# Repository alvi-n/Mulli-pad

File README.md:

# Mullipad
> By Alvin Nguyen

## 5-Key Macropad featuring: 
- Rotary Encoder (Knob)
- Full RGB backlighting using Neopixels 
- Small OLED screen 
- Recessed Base to give a _"floating"_ effect 
  
| "Woah this looks pretty cool" | "Same with this inside" |
| ----- | ---- |
|  |  |

## Details
This was a fun 3-week project to learn about PCB making, and it was fun modeling the case. It took a lot of questions on Slack and tutorials, but here it is. 

| Schematic | PCB |
| ----- | ---- |
|  |  |

### Future Plans
- I'm planning on using transparent 3d filament for the base so the light can glow on the bottom. This will also be used for my Hack Club at my school as an example project.
- The plate will be glued on...
- **The OLED screen will be connected to the pcb by wires which will be soldered on**

# BOM

| item | quantity |
| --- | --- |
| MX-Style switches | 5 |
| Blank DSA keycaps (White) | 5 |
| 0.91 inch OLED display | 1 |
| EC11 rotary encoder | 1 |
| Seeed xiao rp2040 | 1 |
| SK6812 mini-e led | 5 |
| 1x4 pin header | 1 |
| short f/f 1x4 pin header connector | 1 |
| M3x16mm screws | 4 |
| Case (Top, Plate, Bottom) | All 3D printed myself |

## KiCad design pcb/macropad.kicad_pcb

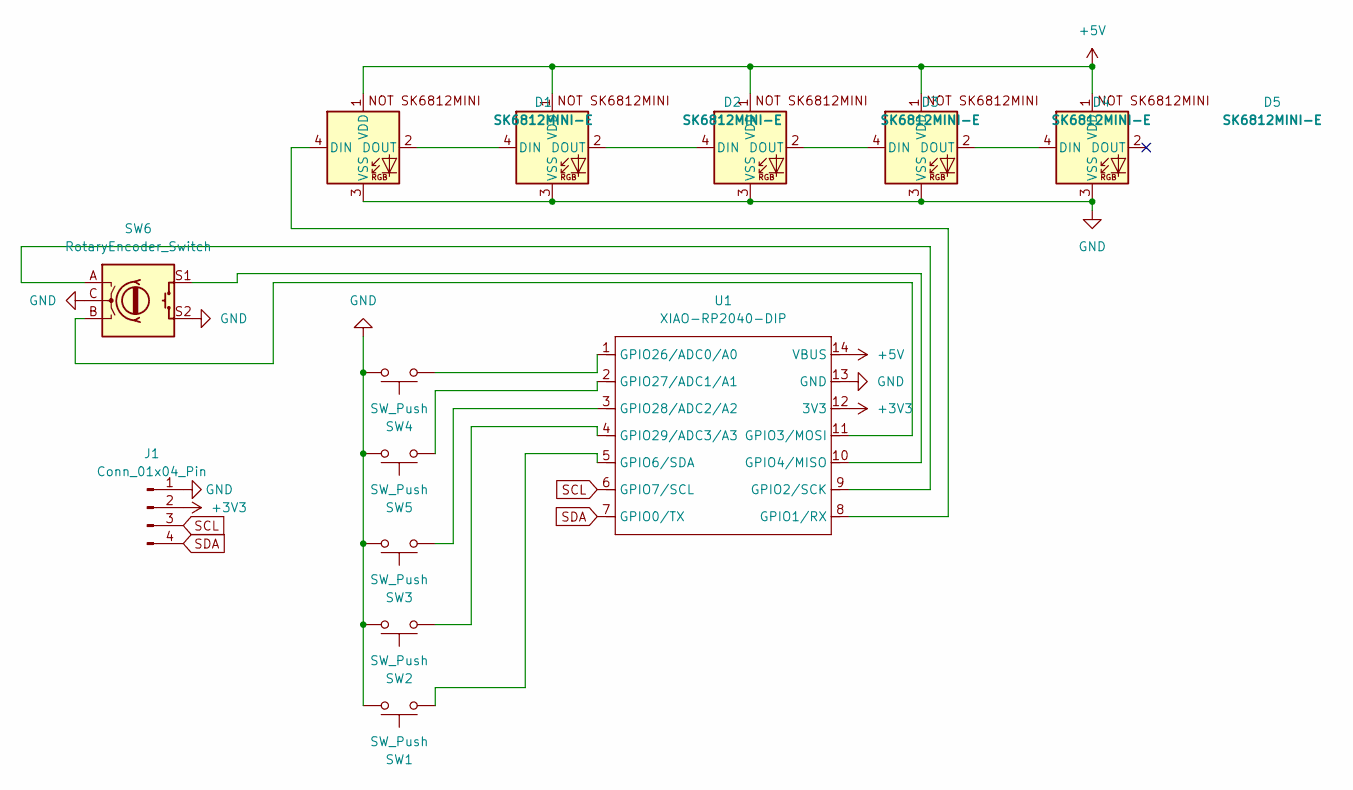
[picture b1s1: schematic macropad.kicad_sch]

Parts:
D1, D2, D3, D4, D5: SK6812MINI-E; SK6812MINI-E_fixed
J1: Conn_01x04_Pin; PinHeader_1x04_P2.54mm_Vertical
SW1, SW2, SW3, SW4, SW5: SW_Push; SW_Cherry_MX_1.00u_PCB
SW6: RotaryEncoder_Switch; RotaryEncoder_Alps_EC11E-Switch_Vertical_H20mm
U1: XIAO-RP2040-DIP

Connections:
+3V3: J1.2, U1.12 (3V3)
+5V: D1.1 (VDD), D2.1 (VDD), D3.1 (VDD), D4.1 (VDD), D5.1 (VDD), U1.14 (VBUS)
GND: D1.3 (VSS), D2.3 (VSS), D3.3 (VSS), D4.3 (VSS), D5.3 (VSS), J1.1, SW1.1, SW2.1, SW3.1, SW4.1, SW5.1, SW6.C, SW6.S2, U1.13 (GND)
unnamed: D1.4 (DIN), U1.8 (GPIO1/RX)
unnamed: D1.2 (DOUT), D2.4 (DIN)
unnamed: D2.2 (DOUT), D3.4 (DIN)
unnamed: D3.2 (DOUT), D4.4 (DIN)
unnamed: D4.2 (DOUT), D5.4 (DIN)
unnamed: SW6.A, U1.9 (GPIO2/SCK)
unnamed: SW6.B, U1.11 (GPIO3/MOSI)
unnamed: SW6.S1, U1.10 (GPIO4/MISO)
unnamed: SW1.2, U1.5 (GPIO6/SDA)
unnamed: SW4.2, U1.1 (GPIO26/ADC0/A0)
unnamed: SW5.2, U1.2 (GPIO27/ADC1/A1)
unnamed: SW3.2, U1.3 (GPIO28/ADC2/A2)
unnamed: SW2.2, U1.4 (GPIO29/ADC3/A3)
SCL: J1.3, U1.6 (GPIO7/SCL)
SDA: J1.4, U1.7 (GPIO0/TX)

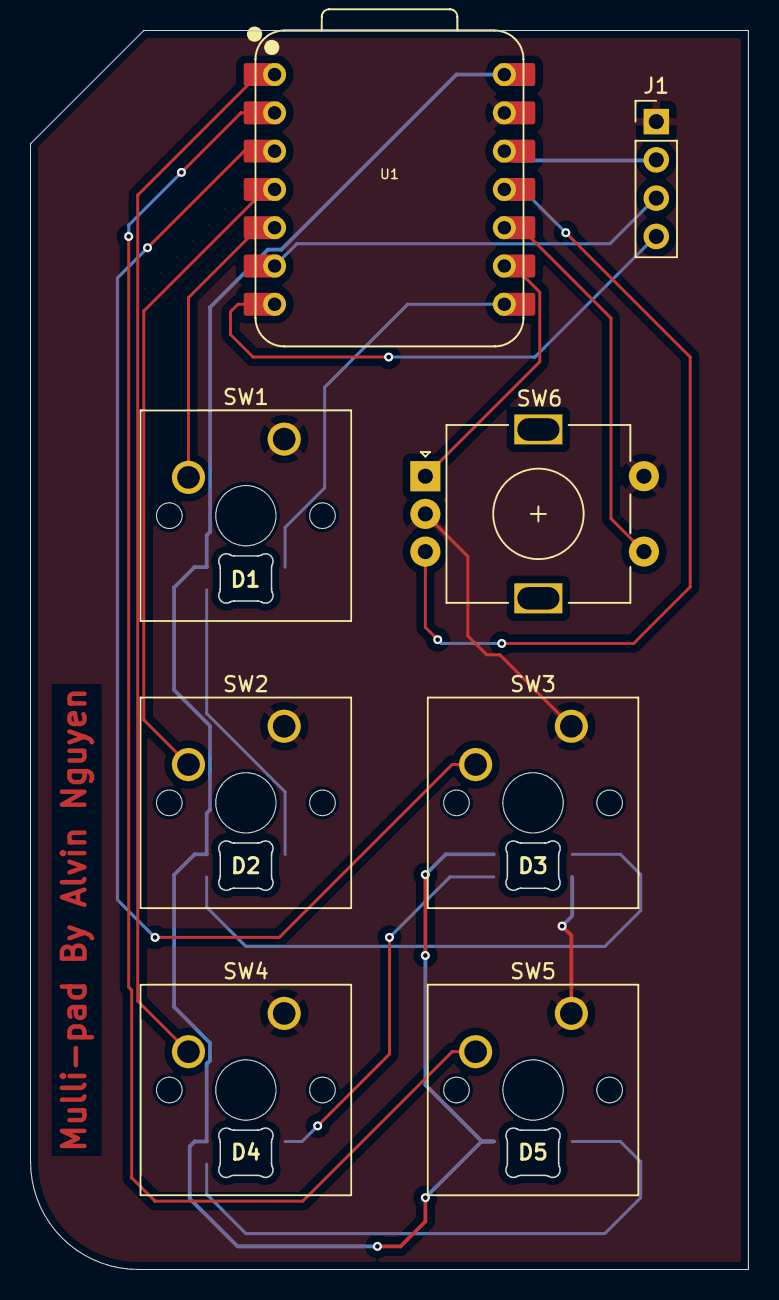
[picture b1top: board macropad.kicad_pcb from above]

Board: 2 copper layers, 47.6 x 82.1 mm, 13 parts (0 on the bottom side), 18 nets.

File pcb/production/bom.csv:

Designator,Footprint,Quantity,Value,LCSC Part #
"D1, D2, D3, D4, D5",SK6812MINI-E_fixed,5,SK6812MINI-E,
J1,PinHeader_1x04_P2.54mm_Vertical,1,Conn_01x04_Pin,
"SW1, SW2, SW3, SW4, SW5",SW_Cherry_MX_1.00u_PCB,5,SW_Push,
SW6,RotaryEncoder_Alps_EC11E-Switch_Vertical_H20mm,1,RotaryEncoder_Switch,
U1,XIAO-RP2040-DIP,1,XIAO-RP2040-DIP,

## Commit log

2026-01-30 Upload all project folders
2026-02-02 Got rid of emoji
2026-02-06 Changed CAD file type, Updated Image
